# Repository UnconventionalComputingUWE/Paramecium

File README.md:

# Paramecium
Contained in this github are files to create and test artificial cilia.

%%%% Board manufacture %%%%
The eagle files are included in the github so that users may produce articifial cilia. There is a free version of EagleCAD for all users which allows for the modification and design of 2 layered boards, so anyone can edit the files. Some board manufacturers accept EagleCad files however some companies only accept Gerber files; there is a simple method of converting EagleCAD designs to Gerbers in the software.

%%%% Assembling the boards %%%%
The parts can be assembled on the boards by the user or by the board manufacturer should they have such capabilities. Some components are through-hole and some are surface-mount; both can be soldered by hand by anyone with reasonable soldering proficiency.

%%%% Uploading files to the board %%%%
You must upload the hex files (both the supplied one, and user created ones) using an ISP.
We used AVRDUDE to upload hex files via a USBtinyISP AVR Programmer Kit (USB SpokePOV Dongle) - v2.0. Other ISP devices may work.

Anyone is free to use and modify these designs and code for their use. Please provide appropriate credit, such as citations. Commercial use is permitted.

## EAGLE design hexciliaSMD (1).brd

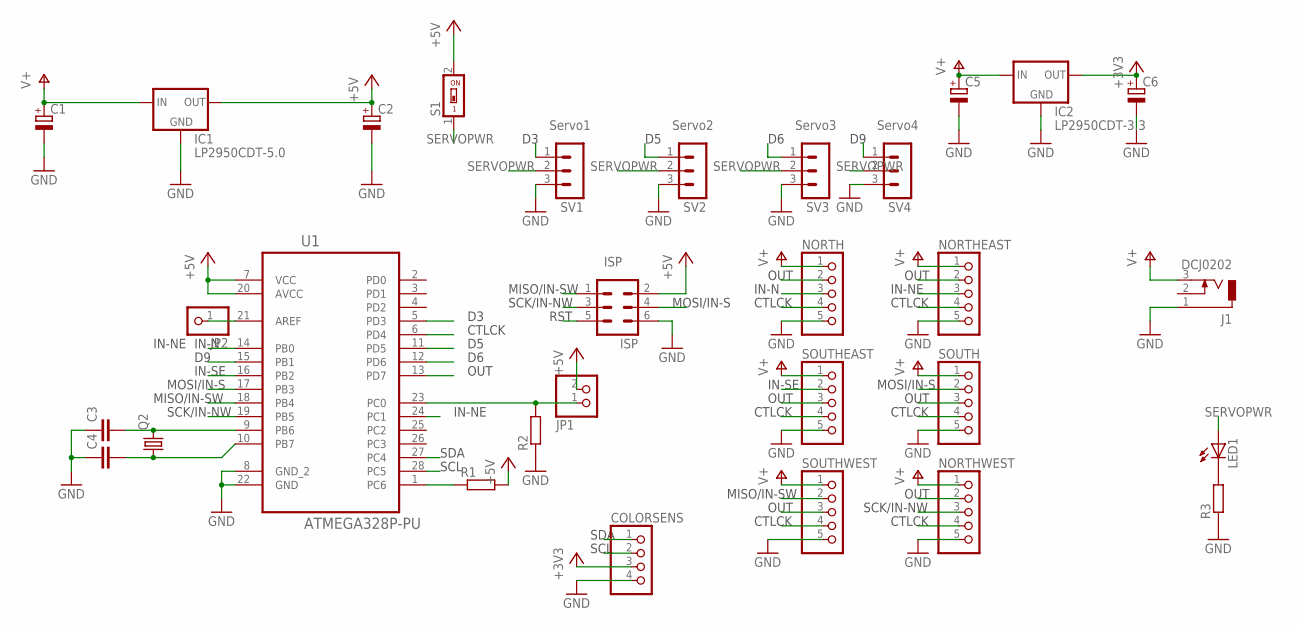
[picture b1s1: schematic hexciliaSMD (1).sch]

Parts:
C1, C2, C5, C6: CPOL-EU153CLV-0605; 153CLV-0605
C3, C4: C-EUC1210; C1210
COLORSENS: PINHD-1X4; 1X04
IC1: LP2950CDT-5.0; DPACK
IC2: LP2950CDT-3.3; DPACK
ISP: MA03-2
J1: DCJ0202
JP1: PINHD-1X2; 1X02
JP2: PINHD-1X1; 1X01
LED1: LEDCHIP-LED0805; CHIP-LED0805
NORTH: PINHD-1X5; 1X05
NORTHEAST: PINHD-1X5; 1X05
NORTHWEST: PINHD-1X5; 1X05
Q2: CRYSTALHC49UP; HC49UP
R1, R2, R3: R-EU_M1206; M1206
S1: SWS001; SMS-001
SOUTH: PINHD-1X5; 1X05
SOUTHEAST: PINHD-1X5; 1X05
SOUTHWEST: PINHD-1X5; 1X05
SV1, SV2, SV3, SV4: MA03-1
U1: ATMEGA328P-PU; DIP254P762X457-28

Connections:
+3V3: C6.+, COLORSENS.3, IC2.3 (OUT)
+5V: C2.+, IC1.3 (OUT), ISP.2, JP1.2, R1.2, S1.2, U1.7 (VCC), U1.20 (AVCC)
CONTROLCK: NORTH.4, NORTHEAST.4, NORTHWEST.4, SOUTH.4, SOUTHEAST.4, SOUTHWEST.4, U1.6 (PD4)
CTLCHK: JP1.1, R2.2, U1.23 (PC0)
D3: SV1.1, U1.5 (PD3)
D5: SV2.1, U1.11 (PD5)
D6: SV3.1, U1.12 (PD6)
D9: SV4.1, U1.15 (PB1)
GND: C1.-, C2.-, C3.1, C4.1, C5.-, C6.-, COLORSENS.4, IC1.4 (GND), IC2.4 (GND), ISP.6, J1.1, NORTH.5, NORTHEAST.5, NORTHWEST.5, R2.1, R3.1, SOUTH.5, SOUTHEAST.5, SOUTHWEST.5, SV1.3, SV2.3, SV3.3, SV4.3, U1.8 (GND_2), U1.22 (GND)
IN-N: NORTH.3, U1.14 (PB0)
IN-NE: NORTHEAST.3, U1.24 (PC1)
IN-SE: SOUTHEAST.2, U1.16 (PB2)
MISO/IN-SW: ISP.1, SOUTHWEST.2, U1.18 (PB4)
MOSI/IN-S: ISP.4, SOUTH.2, U1.17 (PB3)
unnamed: JP2.1, U1.21 (AREF)
unnamed: LED1.C, R3.2
unnamed: C3.2, Q2.2, U1.9 (PB6)
unnamed: C4.2, Q2.1, U1.10 (PB7)
OUT: NORTH.2, NORTHEAST.2, NORTHWEST.2, SOUTH.3, SOUTHEAST.3, SOUTHWEST.3, U1.13 (PD7)
RST: ISP.5, R1.1, U1.1 (PC6)
SCK/IN-NW: ISP.3, NORTHWEST.3, U1.19 (PB5)
SCL: COLORSENS.2, U1.28 (PC5)
SDA: COLORSENS.1, U1.27 (PC4)
SWPWR: LED1.A, S1.1, SV1.2, SV2.2, SV3.2, SV4.2
V+: C1.+, C5.+, IC1.1 (IN), IC2.1 (IN), J1.3, NORTH.1, NORTHEAST.1, NORTHWEST.1, SOUTH.1, SOUTHEAST.1, SOUTHWEST.1

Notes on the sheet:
Servo1
Servo2
Servo3
ISP
CTLCK
OUT
SDA
SCL
IN-N
IN-NE
IN-SE
MOSI/IN-S
MISO/IN-SW
SCK/IN-NW
RST
Servo4
SERVOPWR

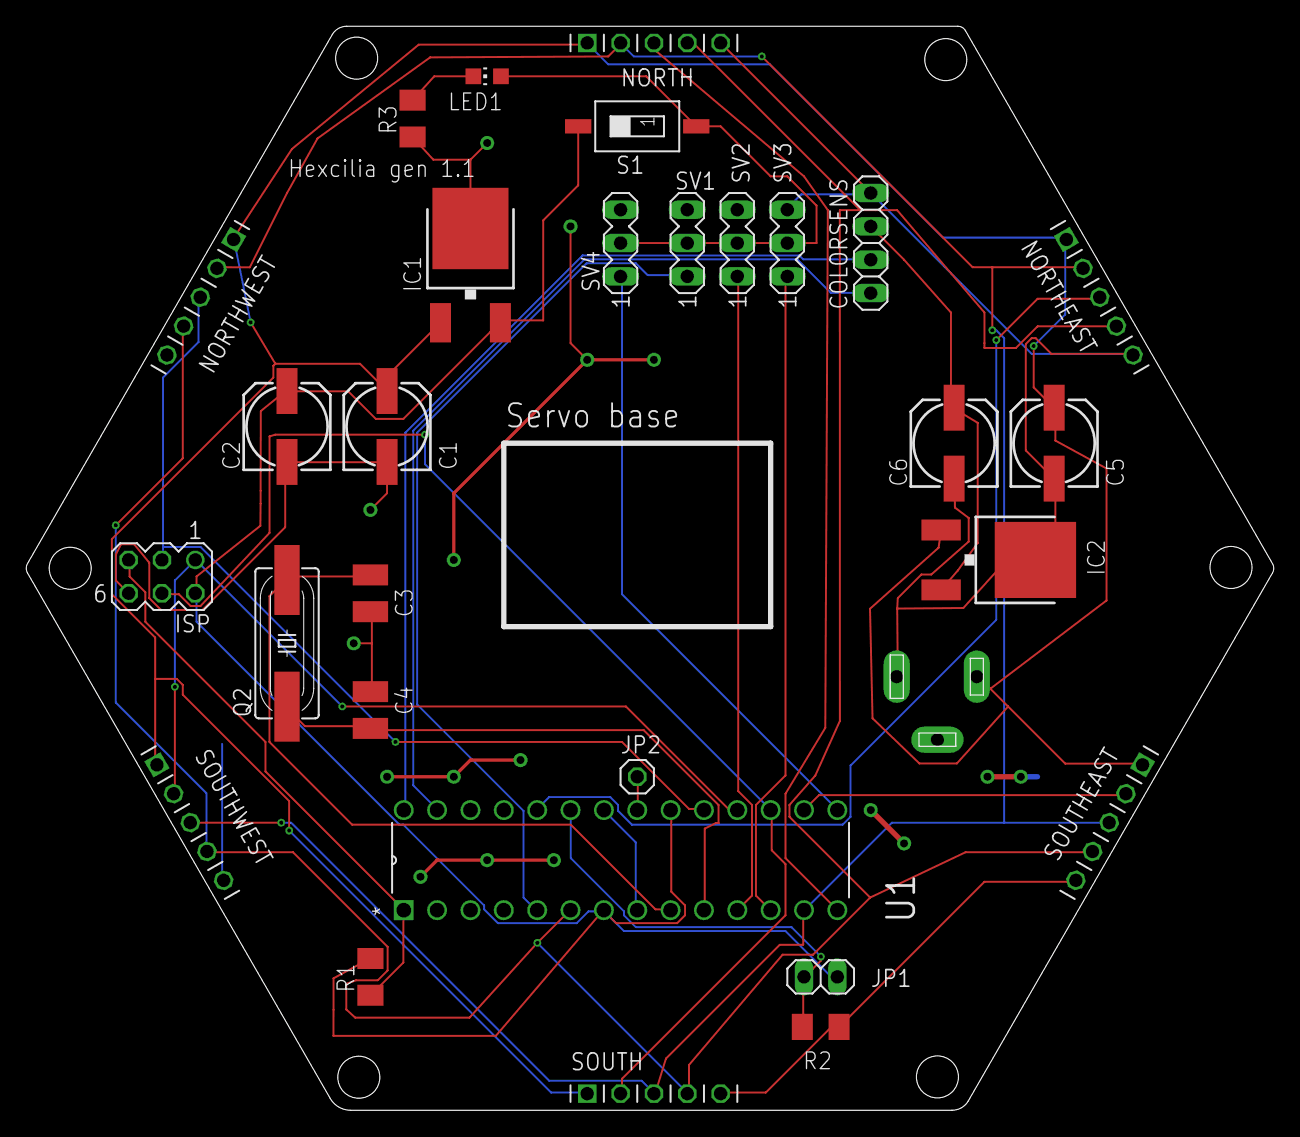
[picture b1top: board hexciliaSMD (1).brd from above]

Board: 4 copper layers, 95.0 x 82.5 mm, 30 parts (1 on the bottom side), 25 nets.
